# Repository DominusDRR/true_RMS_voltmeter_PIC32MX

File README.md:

# true_RMS_voltmeter_PIC32MX
AC voltmeter (true RMS) to measure 120VAC with a PIC32 microcontroller.

Project Description
This project features an alternating current (AC) voltmeter capable of measuring up to ±300V peak and a highly accurate frequency meter.

Key Features:
TRUE RMS Measurement: The device computes precise mathematical calculations on the analyzed signal to deliver an accurate true RMS value.
Frequency Meter: Accurately measures the frequency of the input AC signal, making it versatile for various applications.
Self-Powered Design: No external power source is required. The circuit is powered directly from the analyzed signal itself.

## [a. Project Concept.](ProjectConcept.md)
## [b. Signal conditioning circuit.](SignalConditioningCircuit.md)
## [c. Active filter design.](ActiveFilterDesign.md)
## [d. Assignment of microcontroller pins or terminals.](AssignmentMicrocontrollerPinsTerminals.md)
## [e. Simulation of the signal conditioning circuit.](SimulationSignalConditioningCircuit.md)
## [f. Signal conditioning testing with prototype hardware.](SignalConditioning.md)
## [g. PCB Layout.](PCBLayout.md)
## [h. RMS value calculation analysis.](RMSCalueCalculationAnalysis.md)  
## [i. Creating microcontroller code.](CreatingMicrocontrollerCode.md) 
## [j. Process of acquiring analog signal samples with the ADC.](ADC.md)
## [k. Task that controls the acoustic signal (buzzer).](Buzzer.md)
## [l. Task that manages the 7‐segment display.](Display.md)
## [m. Task that performs the RMS calculation.](RMS.md)
## [n. Task that manages the push button.](PushButton.md)

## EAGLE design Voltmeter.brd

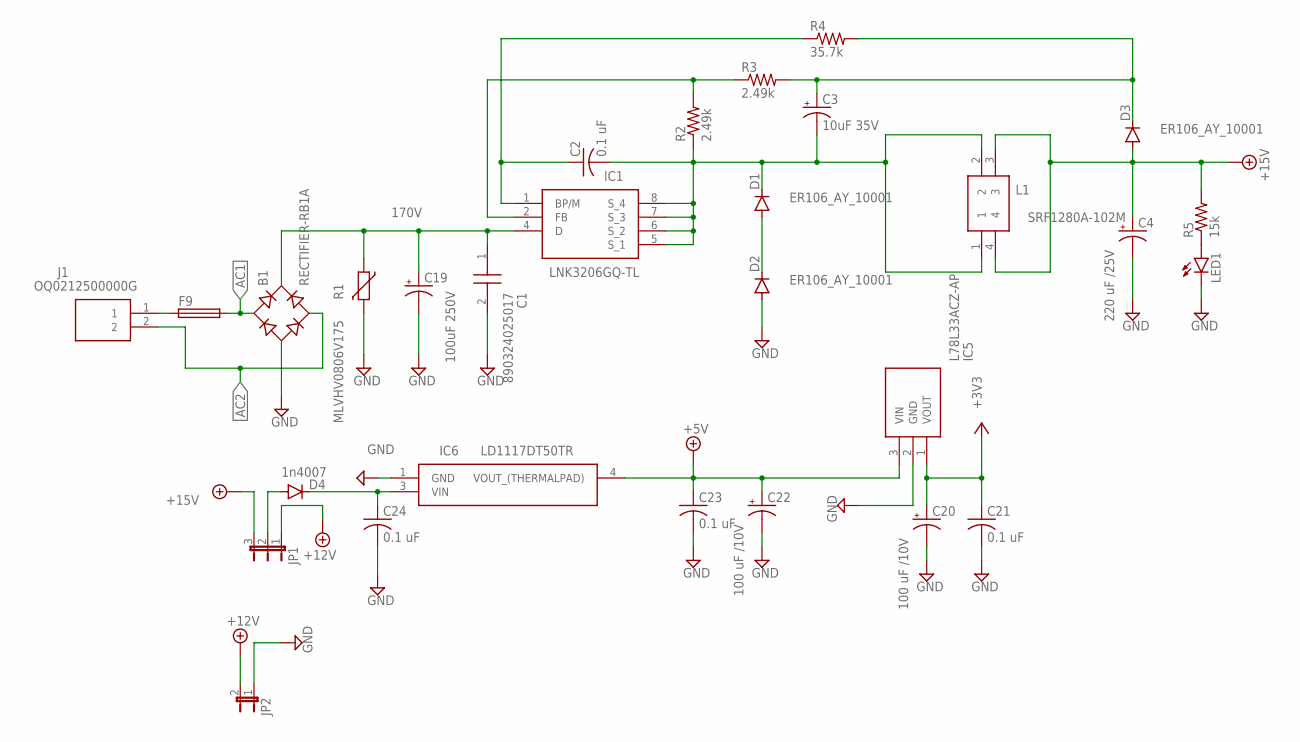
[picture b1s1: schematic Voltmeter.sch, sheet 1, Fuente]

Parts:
B1: RECTIFIER-RB1A; RB1A
C1: 890324025017
C2, C21, C23, C24: 0.1 uF; C0603K
C3: 10uF 35V; E2,5-6
C4: 220 uF /25V; E3,5-8
C19: 100uF 250V; E5-10,5
C20, C22: 100 uF /10V; E2-5
D1, D2, D3: ER106_AY_10001; DO41-7.6
D4: 1n4007; DO41-7.6
F9: LITTLEFUSE
IC1: LNK3206GQ-TL; TOP253GNTL
IC5: L78L33ACZ-AP; TS1107A1AP
IC6: LD1117DT50TR; TO228P972X240-3N
J1: OQ0212500000G
JP1: JP2E; JP2
JP2: JP1E; JP1
L1: SRF1280A-102M; SRF1280A102M
LED1: LEDSML0805; SML0805
R1: MLVHV0806V175; CT/CN1206
R2, R3: 2.49k; R0603
R4: 35.7k; R0805
R5: 15k; R0603

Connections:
170V: B1.+, C1.1, C19.+, IC1.4 (D), R1.1
+3V3: C20.+, C21.1, IC5.1 (VOUT); also elsewhere on the board
+5V: C22.+, C23.1, IC5.3 (VIN), IC6.4 (VOUT_(THERMALPAD)); also elsewhere on the board
+12V: JP1.1, JP2.2
+15V: C4.+, D3.A, JP1.3, L1.3, L1.4, R5.2
AC1: B1.AC1, F9.2; also elsewhere on the board
AC2: B1.AC2, J1.2; also elsewhere on the board
GND: B1.-, C1.2, C4.-, C19.-, C20.-, C21.2, C22.-, C23.2, C24.2, D2.A, IC5.2 (GND), IC6.1 (GND), JP2.1, LED1.C, R1.2; also elsewhere on the board
unnamed: C2.1, IC1.1 (BP/M), R4.1
unnamed: C2.2, C3.-, D1.C, IC1.5 (S_1), IC1.6 (S_2), IC1.7 (S_3), IC1.8 (S_4), L1.1, L1.2, R2.1
unnamed: IC1.2 (FB), R2.2, R3.1
unnamed: C3.+, D3.C, R3.2, R4.2
unnamed: D1.A, D2.C
unnamed: D4.A, JP1.2
unnamed: LED1.A, R5.1
unnamed: C24.1, D4.C, IC6.3 (VIN)
unnamed: F9.1, J1.1

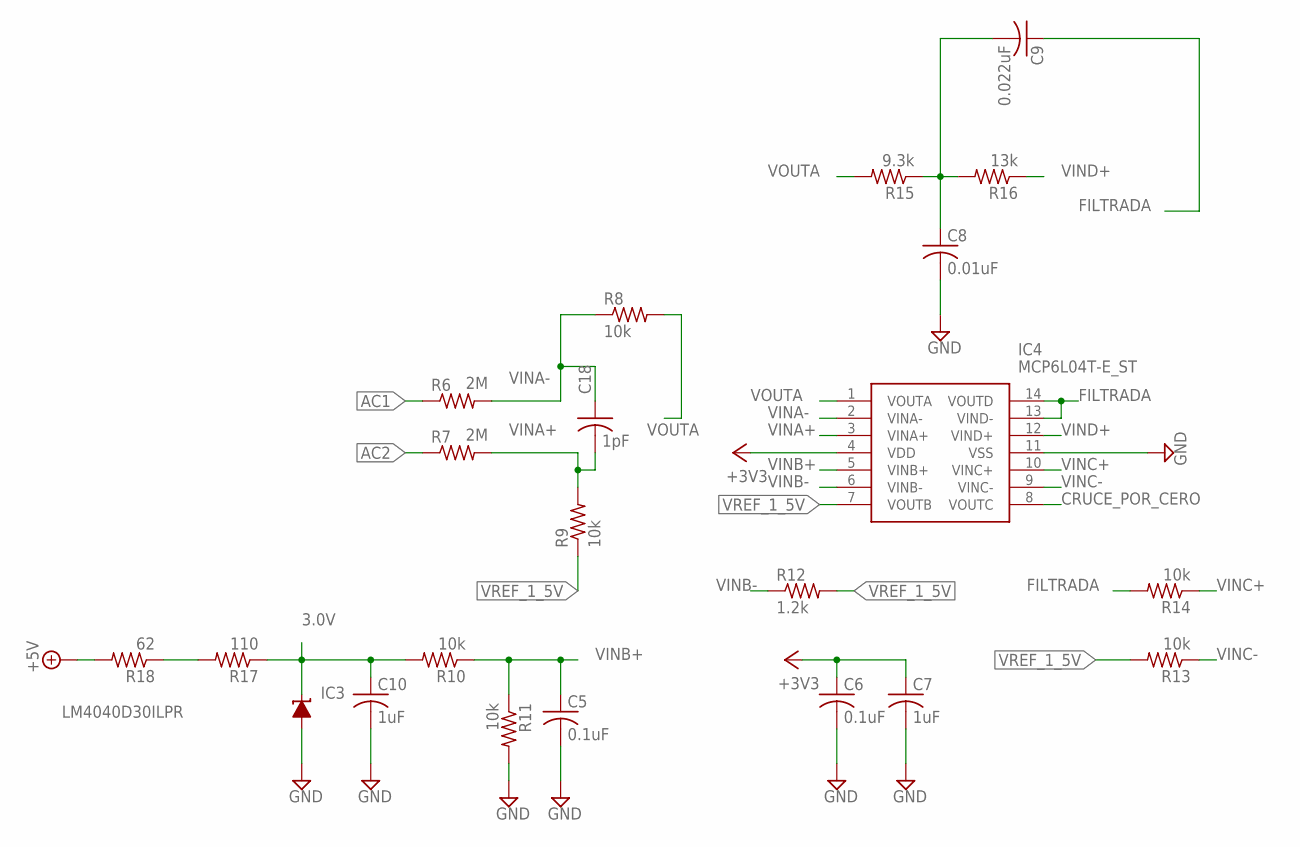
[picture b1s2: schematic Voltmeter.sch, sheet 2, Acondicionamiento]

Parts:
C5, C6: 0.1uF; C0603K
C7, C10: 1uF; C0603K
C8: 0.01uF; C0603K
C9: 0.022uF; C0603K
C18: 1pF; C0603K
IC3: LM4040D30ILPR; LP_O-PBCY-W3
IC4: MCP6L04T-E_ST; SOP65P640X120-14N
R6, R7: 2M; R0603
R8, R9, R10, R11, R13, R14: 10k; R0603
R12: 1.2k; R0603
R15: 9.3k; R0603
R16: 13k; R0603
R17: 110; R0603
R18: 62; R0603

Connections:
3.0V: C10.1, IC3.2 (C), R10.2, R17.1; also elsewhere on the board
+3V3: C6.1, C7.1, IC4.4 (VDD); also elsewhere on the board
+5V: R18.2; also elsewhere on the board
AC1: R6.1; also elsewhere on the board
AC2: R7.1; also elsewhere on the board
CRUCE_POR_CERO: IC4.8 (VOUTC); also elsewhere on the board
FILTRADA: C9.1, IC4.13 (VIND-), IC4.14 (VOUTD), R14.2; also elsewhere on the board
GND: C5.2, C6.2, C7.2, C8.2, C10.2, IC3.3 (A), IC4.11 (VSS), R11.2; also elsewhere on the board
unnamed: C8.1, C9.2, R15.1, R16.2
unnamed: R17.2, R18.1
VINA+: C18.2, IC4.3 (VINA+), R7.2, R9.2
VINA-: C18.1, IC4.2 (VINA-), R6.2, R8.1
VINB+: C5.1, IC4.5 (VINB+), R10.1, R11.1
VINB-: IC4.6 (VINB-), R12.1
VINC+: IC4.10 (VINC+), R14.1
VINC-: IC4.9 (VINC-), R13.1
VIND+: IC4.12 (VIND+), R16.1
VOUTA: IC4.1 (VOUTA), R8.2, R15.2
VREF_1_5V: IC4.7 (VOUTB), R9.1, R12.2, R13.2

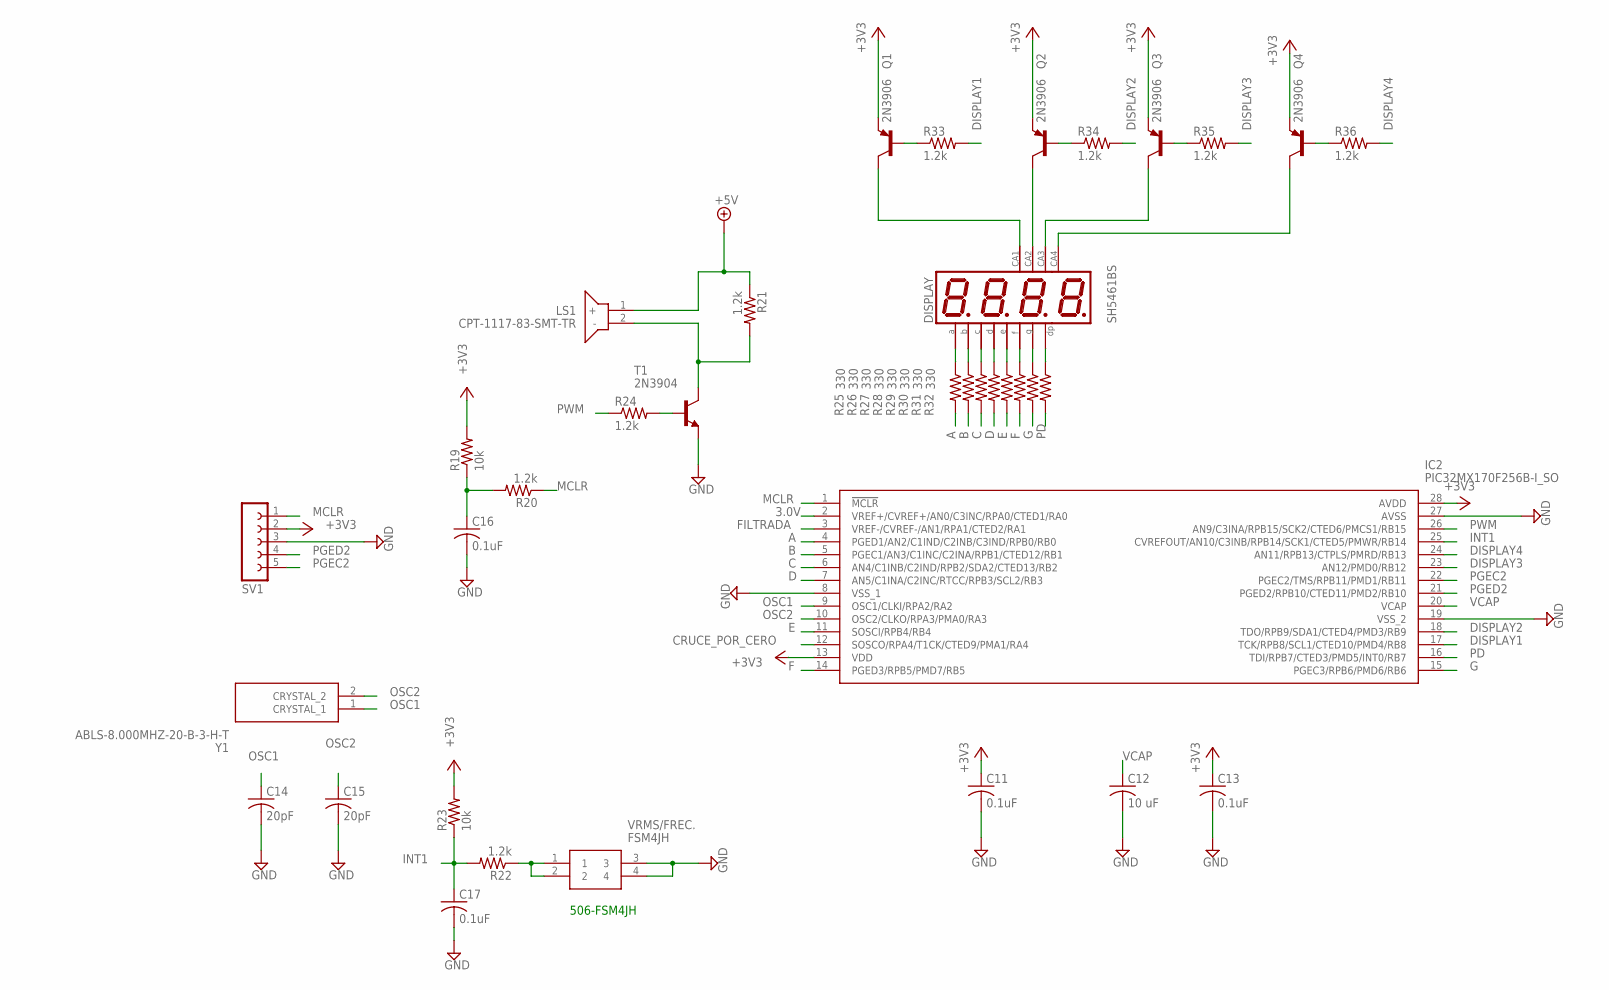
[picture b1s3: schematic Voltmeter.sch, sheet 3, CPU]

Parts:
C11, C13, C16, C17: 0.1uF; C0603K
C12: 10 uF; C1206
C14, C15: 20pF; C0603K
DISPLAY: SH5461BS; BX56_FR3
IC2: PIC32MX170F256B-I_SO; SOIC127P1030X265-28N
LS1: CPT-1117-83-SMT-TR; CPT111783SMTTR
Q1, Q2, Q3, Q4: 2N3906; TO92
R19, R23: 10k; R0603
R20, R21, R22, R24, R33, R34, R35, R36: 1.2k; R0603
R25, R26, R27, R28, R29, R30, R31, R32: 330; R0603
SV1: FE05-1
T1: 2N3904; TO92
VRMS/FREC.: FSM4JH
Y1: ABLS-8.000MHZ-20-B-3-H-T; ABLS8000MHZ20B3HT

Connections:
3.0V: IC2.2 (VREF+/CVREF+/AN0/C3INC/RPA0/CTED1/RA0); also elsewhere on the board
+3V3: C11.1, C13.1, IC2.13 (VDD), IC2.28 (AVDD), Q1.3 (E), Q2.3 (E), Q3.3 (E), Q4.3 (E), R19.2, R23.2, SV1.2; also elsewhere on the board
+5V: LS1.1 (+), R21.1; also elsewhere on the board
A: IC2.4 (PGED1/AN2/C1IND/C2INB/C3IND/RPB0/RB0), R25.2
B: IC2.5 (PGEC1/AN3/C1INC/C2INA/RPB1/CTED12/RB1), R26.2
C: IC2.6 (AN4/C1INB/C2IND/RPB2/SDA2/CTED13/RB2), R27.2
CRUCE_POR_CERO: IC2.12 (SOSCO/RPA4/T1CK/CTED9/PMA1/RA4); also elsewhere on the board
D: IC2.7 (AN5/C1INA/C2INC/RTCC/RPB3/SCL2/RB3), R28.2
DISPLAY1: IC2.17 (TCK/RPB8/SCL1/CTED10/PMD4/RB8), R33.2
DISPLAY2: IC2.18 (TDO/RPB9/SDA1/CTED4/PMD3/RB9), R34.2
DISPLAY3: IC2.23 (AN12/PMD0/RB12), R35.2
DISPLAY4: IC2.24 (AN11/RPB13/CTPLS/PMRD/RB13), R36.2
E: IC2.11 (SOSCI/RPB4/RB4), R29.2
F: IC2.14 (PGED3/RPB5/PMD7/RB5), R30.2
FILTRADA: IC2.3 (VREF-/CVREF-/AN1/RPA1/CTED2/RA1); also elsewhere on the board
G: IC2.15 (PGEC3/RPB6/PMD6/RB6), R31.2
GND: C11.2, C12.2, C13.2, C14.2, C15.2, C16.2, C17.2, IC2.8 (VSS_1), IC2.19 (VSS_2), IC2.27 (AVSS), SV1.3, T1.3 (E), VRMS/FREC..3, VRMS/FREC..4; also elsewhere on the board
INT1: C17.1, IC2.25 (CVREFOUT/AN10/C3INB/RPB14/SCK1/CTED5/PM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), R22.2, R23.1
MCLR: IC2.1 (!MCLR), R20.1, SV1.1
unnamed: C16.1, R19.1, R20.2
unnamed: LS1.2 (-), R21.2, T1.1 (C)
unnamed: R24.2, T1.2 (B)
unnamed: R22.1, VRMS/FREC..1, VRMS/FREC..2
unnamed: DISPLAY.11 (A), R25.1
unnamed: DISPLAY.12 (CA), Q1.1 (C)
unnamed: DISPLAY.7 (B), R26.1
unnamed: DISPLAY.4 (C), R27.1
unnamed: DISPLAY.2 (D), R28.1
unnamed: DISPLAY.1 (E), R29.1
unnamed: DISPLAY.10 (F), R30.1
unnamed: DISPLAY.5 (G), R31.1
unnamed: DISPLAY.3 (DP), R32.1
unnamed: Q1.2 (B), R33.1
unnamed: DISPLAY.9 (CA), Q2.1 (C)
unnamed: DISPLAY.8 (CA), Q3.1 (C)
unnamed: DISPLAY.6 (CA), Q4.1 (C)
unnamed: Q2.2 (B), R34.1
unnamed: Q3.2 (B), R35.1
unnamed: Q4.2 (B), R36.1
OSC1: C14.1, IC2.9 (OSC1/CLKI/RPA2/RA2), Y1.1 (CRYSTAL_1)
OSC2: C15.1, IC2.10 (OSC2/CLKO/RPA3/PMA0/RA3), Y1.2 (CRYSTAL_2)
PD: IC2.16 (TDI/RPB7/CTED3/PMD5/INT0/RB7), R32.2
PGEC2: IC2.22 (PGEC2/TMS/RPB11/PMD1/RB11), SV1.5
PGED2: IC2.21 (PGED2/RPB10/CTED11/PMD2/RB10), SV1.4
PWM: IC2.26 (AN9/C3INA/RPB15/SCK2/CTED6/PMCS1/RB15), R24.1
VCAP: C12.1, IC2.20 (VCAP)

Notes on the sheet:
506-FSM4JH

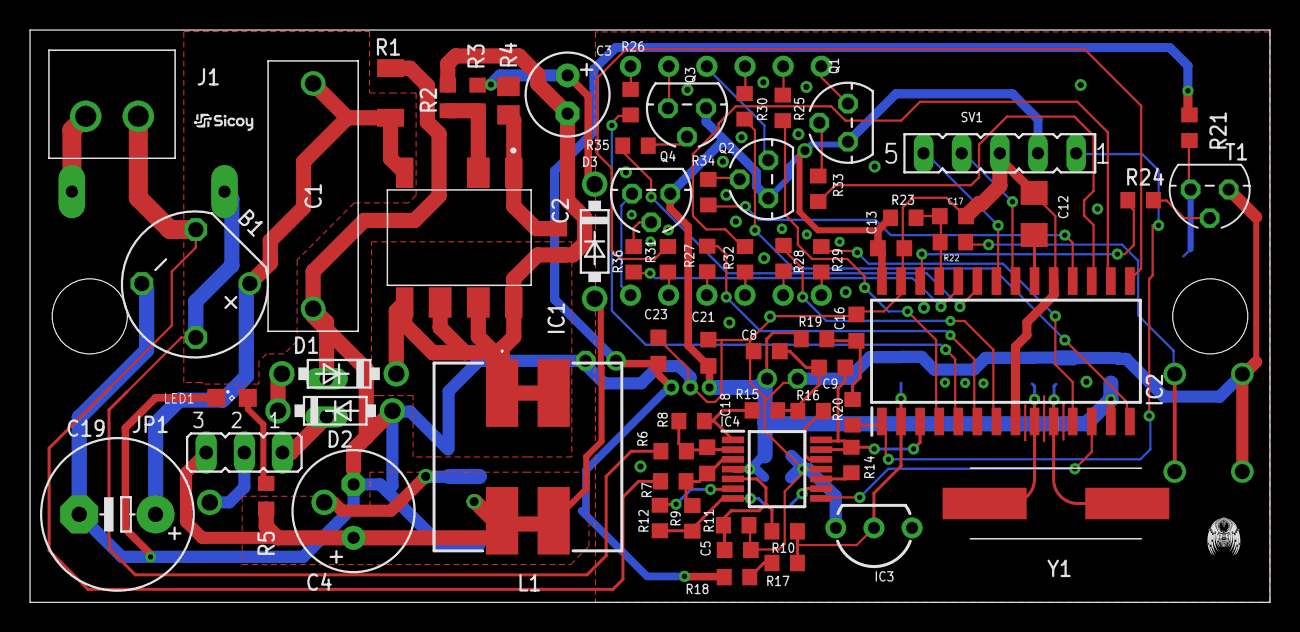
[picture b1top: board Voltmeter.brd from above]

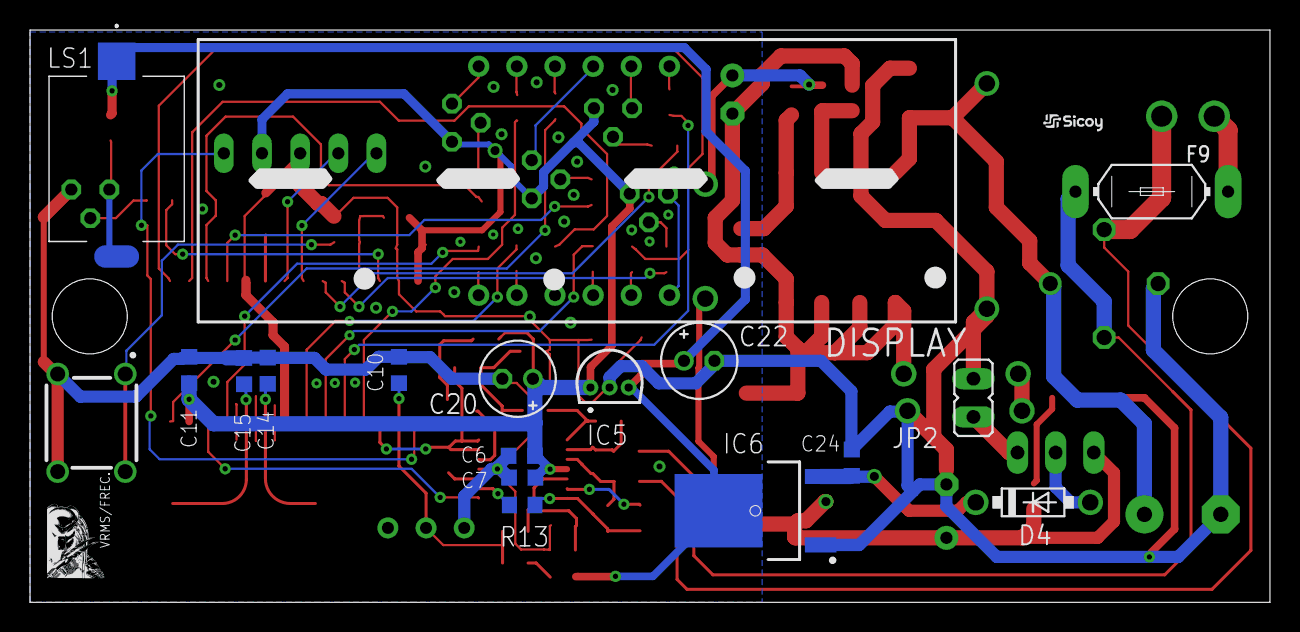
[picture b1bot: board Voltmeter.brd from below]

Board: 2 copper layers, 82.5 x 38.1 mm, 87 parts (18 on the bottom side), 71 nets.

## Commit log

2024-11-28 Voltmeter PCB created in EAGLE PCB
2024-12-01 Create LICENSE
2024-12-01 Update README.md
    Added a slightly more detailed description
2024-12-02 Update README.md
    https://www.youtube.com/watch?v=dqBPHb_SDKo
2024-12-02 Update README.md
    Video link related to image
2024-12-12 Hexadecimal file
    Hexadecimal file of the voltmeter project with the PIC32MX170F256B microcontroller
